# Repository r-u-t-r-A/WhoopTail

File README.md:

# WhoopTail
Battery pigtail pcb with leds

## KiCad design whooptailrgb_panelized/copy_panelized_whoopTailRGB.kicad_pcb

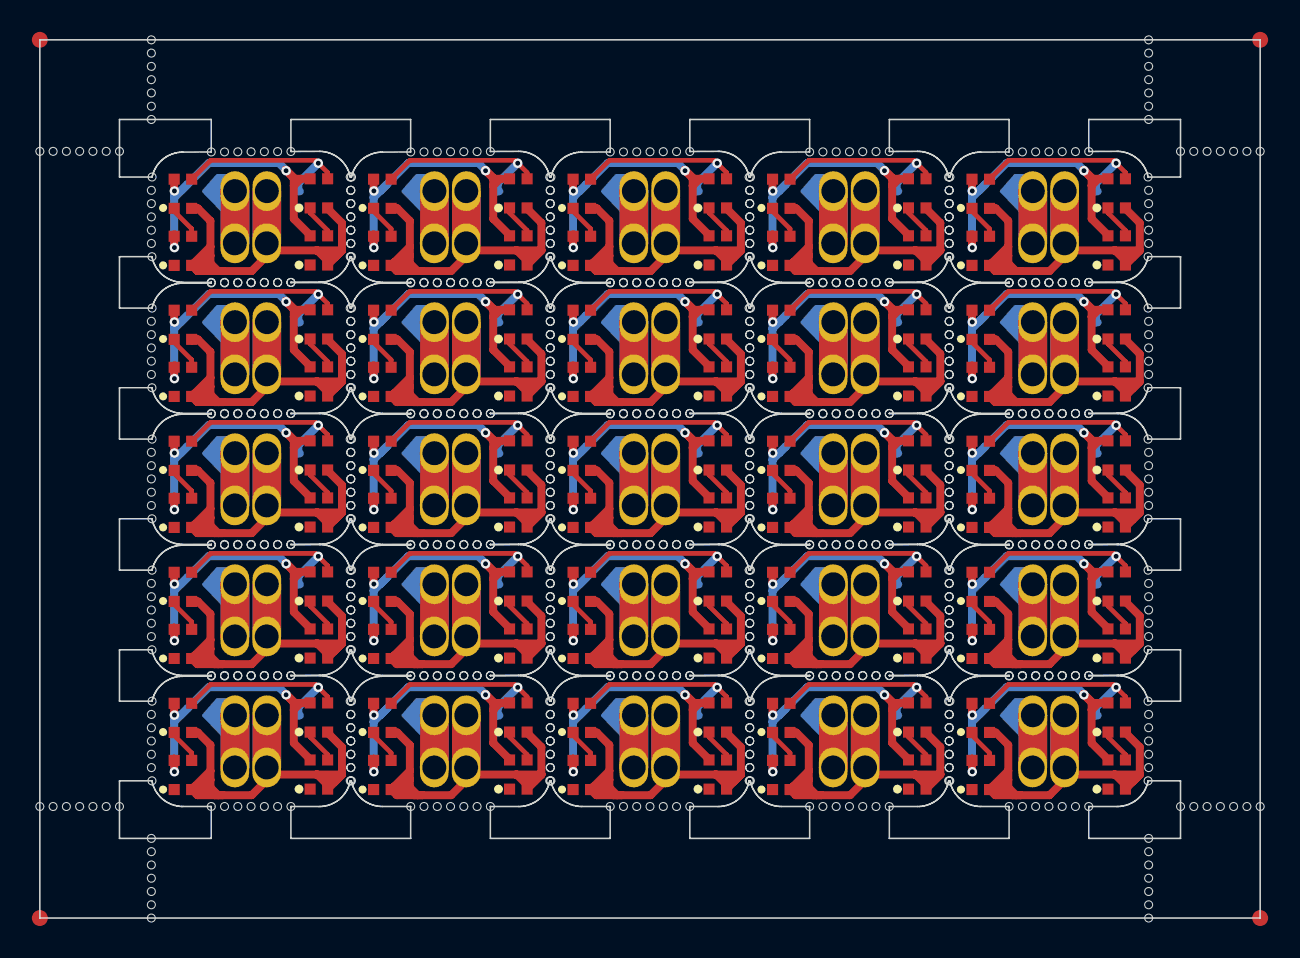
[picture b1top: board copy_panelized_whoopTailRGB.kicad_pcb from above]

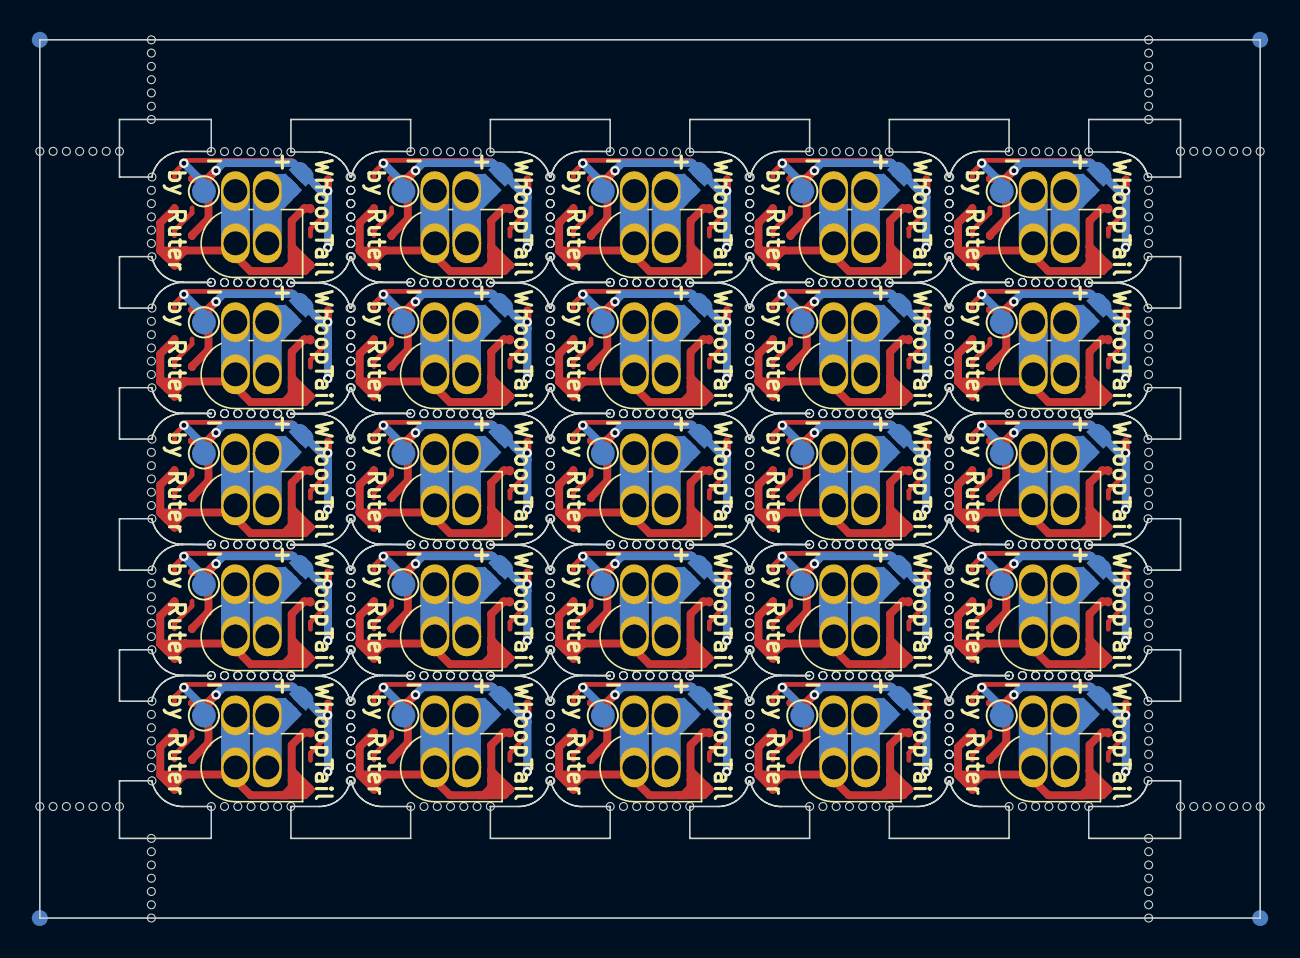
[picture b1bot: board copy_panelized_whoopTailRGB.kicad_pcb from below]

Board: 2 copper layers, 76.6 x 55.1 mm, 964 parts (54 on the bottom side), 150 nets.

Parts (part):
D1, D1#2, D1#3, D1#4, D1#5, D1#6, D1#7, D1#8, D1#9, D1#10, D1#11, D1#12, D1#13, D1#14, D1#15, D1#16, D1#17, D1#18, D1#19, D1#20, D1#21, D1#22, D1#23, D1#24, D1#25, D2, D2#2, D2#3, D2#4, D2#5, D2#6, D2#7, D2#8, D2#9, D2#10, D2#11, D2#12, D2#13, D2#14, D2#15, D2#16, D2#17, D2#18, D2#19, D2#20, D2#21, D2#22, D2#23, D2#24, D2#25, D3, D3#2, D3#3, D3#4, D3#5, D3#6, D3#7, D3#8, D3#9, D3#10, D3#11, D3#12, D3#13, D3#14, D3#15, D3#16, D3#17, D3#18, D3#19, D3#20, D3#21, D3#22, D3#23, D3#24, D3#25, D4, D4#2, D4#3, D4#4, D4#5, D4#6, D4#7, D4#8, D4#9, D4#10, D4#11, D4#12, D4#13, D4#14, D4#15, D4#16, D4#17, D4#18, D4#19, D4#20, D4#21, D4#22, D4#23, D4#24, D4#25: WS2812B-2020; LED_WS2812B-2020_PLCC4_2.0x2.0mm
J1, J1#2, J1#3, J1#4, J1#5, J1#6, J1#7, J1#8, J1#9, J1#10, J1#11, J1#12, J1#13, J1#14, J1#15, J1#16, J1#17, J1#18, J1#19, J1#20, J1#21, J1#22, J1#23, J1#24, J1#25: BT20; PinHeader_1x02_P2.00mm_Vertical
J2, J2#2, J2#3, J2#4, J2#5, J2#6, J2#7, J2#8, J2#9, J2#10, J2#11, J2#12, J2#13, J2#14, J2#15, J2#16, J2#17, J2#18, J2#19, J2#20, J2#21, J2#22, J2#23, J2#24, J2#25: WIRE; PinHeader_1x02_P2.00mm_Vertical
J3, J3#2, J3#3, J3#4, J3#5, J3#6, J3#7, J3#8, J3#9, J3#10, J3#11, J3#12, J3#13, J3#14, J3#15, J3#16, J3#17, J3#18, J3#19, J3#20, J3#21, J3#22, J3#23, J3#24, J3#25: Conn_01x01_Pin; TestPoint_Pad_D1.5mm
J4, J4#2, J4#3, J4#4, J4#5, J4#6, J4#7, J4#8, J4#9, J4#10, J4#11, J4#12, J4#13, J4#14, J4#15, J4#16, J4#17, J4#18, J4#19, J4#20, J4#21, J4#22, J4#23, J4#24, J4#25: Conn_01x02_Pin; SolderJumper-2_P1.3mm_Open_RoundedPad1.0x1.5mm
KiKit_FID_B_1, KiKit_FID_B_2, KiKit_FID_B_3, KiKit_FID_B_4: Fiducial
KiKit_FID_T_1, KiKit_FID_T_2, KiKit_FID_T_3, KiKit_FID_T_4: Fiducial
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
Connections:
Board_0-GND: D1#16.2 (VSS), D2#7.2 (VSS), D3#8.2 (VSS), D4#19.2 (VSS), J1#22.2, J2#14.2
Board_0-Net-(D1-DIN): D1#16.3 (DIN), D3#8.3 (DIN), J3#9.1
Board_0-Net-(D1-DOUT): D1#16.1 (DOUT), D2#7.3 (DIN)
Board_0-Net-(D3-DOUT): D3#8.1 (DOUT), D4#19.3 (DIN)
Board_0-VBAT: J1#22.1, J2#14.1, J4#13.2
Board_0-V_LED: D1#16.4 (VDD), D2#7.4 (VDD), D3#8.4 (VDD), D4#19.4 (VDD), J4#13.1
Board_1-GND: D1#8.2 (VSS), D2#15.2 (VSS), D3#12.2 (VSS), D4#9.2 (VSS), J1#14.2, J2#5.2
Board_1-Net-(D1-DIN): D1#8.3 (DIN), D3#12.3 (DIN), J3#10.1
Board_1-Net-(D1-DOUT): D1#8.1 (DOUT), D2#15.3 (DIN)
Board_1-Net-(D3-DOUT): D3#12.1 (DOUT), D4#9.3 (DIN)
Board_1-VBAT: J1#14.1, J2#5.1, J4#7.2
Board_1-V_LED: D1#8.4 (VDD), D2#15.4 (VDD), D3#12.4 (VDD), D4#9.4 (VDD), J4#7.1
Board_2-GND: D1#11.2 (VSS), D2#18.2 (VSS), D3#11.2 (VSS), D4#14.2 (VSS), J1#17.2, J2#7.2
Board_2-Net-(D1-DIN): D1#11.3 (DIN), D3#11.3 (DIN), J3#16.1
Board_2-Net-(D1-DOUT): D1#11.1 (DOUT), D2#18.3 (DIN)
Board_2-Net-(D3-DOUT): D3#11.1 (DOUT), D4#14.3 (DIN)
Board_2-VBAT: J1#17.1, J2#7.1, J4#8.2
Board_2-V_LED: D1#11.4 (VDD), D2#18.4 (VDD), D3#11.4 (VDD), D4#14.4 (VDD), J4#8.1
Board_3-GND: D1#25.2 (VSS), D2#20.2 (VSS), D3#13.2 (VSS), D4#2.2 (VSS), J1#12.2, J2#23.2
Board_3-Net-(D1-DIN): D1#25.3 (DIN), D3#13.3 (DIN), J3#7.1
Board_3-Net-(D1-DOUT): D1#25.1 (DOUT), D2#20.3 (DIN)
Board_3-Net-(D3-DOUT): D3#13.1 (DOUT), D4#2.3 (DIN)
Board_3-VBAT: J1#12.1, J2#23.1, J4#16.2
Board_3-V_LED: D1#25.4 (VDD), D2#20.4 (VDD), D3#13.4 (VDD), D4#2.4 (VDD), J4#16.1
Board_4-GND: D1#6.2 (VSS), D2#14.2 (VSS), D3#18.2 (VSS), D4#25.2 (VSS), J1#18.2, J2#9.2
Board_4-Net-(D1-DIN): D1#6.3 (DIN), D3#18.3 (DIN), J3#5.1
Board_4-Net-(D1-DOUT): D1#6.1 (DOUT), D2#14.3 (DIN)
Board_4-Net-(D3-DOUT): D3#18.1 (DOUT), D4#25.3 (DIN)
Board_4-VBAT: J1#18.1, J2#9.1, J4#9.2
Board_4-V_LED: D1#6.4 (VDD), D2#14.4 (VDD), D3#18.4 (VDD), D4#25.4 (VDD), J4#9.1
Board_5-GND: D1#5.2 (VSS), D2#5.2 (VSS), D3#9.2 (VSS), D4#20.2 (VSS), J1#16.2, J2#18.2
Board_5-Net-(D1-DIN): D1#5.3 (DIN), D3#9.3 (DIN), J3#19.1
Board_5-Net-(D1-DOUT): D1#5.1 (DOUT), D2#5.3 (DIN)
Board_5-Net-(D3-DOUT): D3#9.1 (DOUT), D4#20.3 (DIN)
Board_5-VBAT: J1#16.1, J2#18.1, J4#5.2
Board_5-V_LED: D1#5.4 (VDD), D2#5.4 (VDD), D3#9.4 (VDD), D4#20.4 (VDD), J4#5.1
Board_6-GND: D1#10.2 (VSS), D2#17.2 (VSS), D3#20.2 (VSS), D4#6.2 (VSS), J1#7.2, J2#4.2
Board_6-Net-(D1-DIN): D1#10.3 (DIN), D3#20.3 (DIN), J3#18.1
Board_6-Net-(D1-DOUT): D1#10.1 (DOUT), D2#17.3 (DIN)
Board_6-Net-(D3-DOUT): D3#20.1 (DOUT), D4#6.3 (DIN)
Board_6-VBAT: J1#7.1, J2#4.1, J4#11.2
Board_6-V_LED: D1#10.4 (VDD), D2#17.4 (VDD), D3#20.4 (VDD), D4#6.4 (VDD), J4#11.1
Board_7-GND: D1#19.2 (VSS), D2#12.2 (VSS), D3#2.2 (VSS), D4#17.2 (VSS), J1#4.2, J2#2.2
Board_7-Net-(D1-DIN): D1#19.3 (DIN), D3#2.3 (DIN), J3#23.1
Board_7-Net-(D1-DOUT): D1#19.1 (DOUT), D2#12.3 (DIN)
Board_7-Net-(D3-DOUT): D3#2.1 (DOUT), D4#17.3 (DIN)
Board_7-VBAT: J1#4.1, J2#2.1, J4#4.2
Board_7-V_LED: D1#19.4 (VDD), D2#12.4 (VDD), D3#2.4 (VDD), D4#17.4 (VDD), J4#4.1
Board_8-GND: D1#2.2 (VSS), D2#8.2 (VSS), D3#25.2 (VSS), D4#24.2 (VSS), J1#15.2, J2#13.2
Board_8-Net-(D1-DIN): D1#2.3 (DIN), D3#25.3 (DIN), J3#8.1
Board_8-Net-(D1-DOUT): D1#2.1 (DOUT), D2#8.3 (DIN)
Board_8-Net-(D3-DOUT): D3#25.1 (DOUT), D4#24.3 (DIN)
Board_8-VBAT: J1#15.1, J2#13.1, J4#20.2
Board_8-V_LED: D1#2.4 (VDD), D2#8.4 (VDD), D3#25.4 (VDD), D4#24.4 (VDD), J4#20.1
Board_9-GND: D1#20.2 (VSS), D2#11.2 (VSS), D3#23.2 (VSS), D4#10.2 (VSS), J1#8.2, J2#22.2
Board_9-Net-(D1-DIN): D1#20.3 (DIN), D3#23.3 (DIN), J3#12.1
Board_9-Net-(D1-DOUT): D1#20.1 (DOUT), D2#11.3 (DIN)
Board_9-Net-(D3-DOUT): D3#23.1 (DOUT), D4#10.3 (DIN)
Board_9-VBAT: J1#8.1, J2#22.1, J4#21.2
Board_9-V_LED: D1#20.4 (VDD), D2#11.4 (VDD), D3#23.4 (VDD), D4#10.4 (VDD), J4#21.1
Board_10-GND: D1#15.2 (VSS), D2#16.2 (VSS), D3#7.2 (VSS), D4#13.2 (VSS), J1#11.2, J2#8.2
Board_10-Net-(D1-DIN): D1#15.3 (DIN), D3#7.3 (DIN), J3#24.1
Board_10-Net-(D1-DOUT): D1#15.1 (DOUT), D2#16.3 (DIN)
Board_10-Net-(D3-DOUT): D3#7.1 (DOUT), D4#13.3 (DIN)
Board_10-VBAT: J1#11.1, J2#8.1, J4#6.2
Board_10-V_LED: D1#15.4 (VDD), D2#16.4 (VDD), D3#7.4 (VDD), D4#13.4 (VDD), J4#6.1
Board_11-GND: D1#14.2 (VSS), D2#19.2 (VSS), D3#19.2 (VSS), D4#16.2 (VSS), J1#3.2, J2#15.2
Board_11-Net-(D1-DIN): D1#14.3 (DIN), D3#19.3 (DIN), J3#3.1
Board_11-Net-(D1-DOUT): D1#14.1 (DOUT), D2#19.3 (DIN)
Board_11-Net-(D3-DOUT): D3#19.1 (DOUT), D4#16.3 (DIN)
Board_11-VBAT: J1#3.1, J2#15.1, J4#3.2
Board_11-V_LED: D1#14.4 (VDD), D2#19.4 (VDD), D3#19.4 (VDD), D4#16.4 (VDD), J4#3.1
Board_12-GND: D1#13.2 (VSS), D2#2.2 (VSS), D3#15.2 (VSS), D4#15.2 (VSS), J1#5.2, J2#21.2
Board_12-Net-(D1-DIN): D1#13.3 (DIN), D3#15.3 (DIN), J3#14.1
Board_12-Net-(D1-DOUT): D1#13.1 (DOUT), D2#2.3 (DIN)
Board_12-Net-(D3-DOUT): D3#15.1 (DOUT), D4#15.3 (DIN)
Board_12-VBAT: J1#5.1, J2#21.1, J4#18.2
Board_12-V_LED: D1#13.4 (VDD), D2#2.4 (VDD), D3#15.4 (VDD), D4#15.4 (VDD), J4#18.1
Board_13-GND: D1#23.2 (VSS), D2#23.2 (VSS), D3#3.2 (VSS), D4#18.2 (VSS), J1#25.2, J2#19.2
Board_13-Net-(D1-DIN): D1#23.3 (DIN), D3#3.3 (DIN), J3#4.1
Board_13-Net-(D1-DOUT): D1#23.1 (DOUT), D2#23.3 (DIN)
Board_13-Net-(D3-DOUT): D3#3.1 (DOUT), D4#18.3 (DIN)
Board_13-VBAT: J1#25.1, J2#19.1, J4#17.2
Board_13-V_LED: D1#23.4 (VDD), D2#23.4 (VDD), D3#3.4 (VDD), D4#18.4 (VDD), J4#17.1
Board_14-GND: D1#17.2 (VSS), D2#4.2 (VSS), D3#4.2 (VSS), D4#11.2 (VSS), J1.2, J2#10.2
Board_14-Net-(D1-DIN): D1#17.3 (DIN), D3#4.3 (DIN), J3#25.1
Board_14-Net-(D1-DOUT): D1#17.1 (DOUT), D2#4.3 (DIN)
Board_14-Net-(D3-DOUT): D3#4.1 (DOUT), D4#11.3 (DIN)
Board_14-VBAT: J1.1, J2#10.1, J4#15.2
Board_14-V_LED: D1#17.4 (VDD), D2#4.4 (VDD), D3#4.4 (VDD), D4#11.4 (VDD), J4#15.1
Board_15-GND: D1#9.2 (VSS), D2#10.2 (VSS), D3#14.2 (VSS), D4#21.2 (VSS), J1#23.2, J2#3.2
Board_15-Net-(D1-DIN): D1#9.3 (DIN), D3#14.3 (DIN), J3#21.1
Board_15-Net-(D1-DOUT): D1#9.1 (DOUT), D2#10.3 (DIN)
Board_15-Net-(D3-DOUT): D3#14.1 (DOUT), D4#21.3 (DIN)
Board_15-VBAT: J1#23.1, J2#3.1, J4#14.2
Board_15-V_LED: D1#9.4 (VDD), D2#10.4 (VDD), D3#14.4 (VDD), D4#21.4 (VDD), J4#14.1
Board_16-GND: D1#4.2 (VSS), D2#22.2 (VSS), D3#17.2 (VSS), D4#12.2 (VSS), J1#6.2, J2#24.2
Board_16-Net-(D1-DIN): D1#4.3 (DIN), D3#17.3 (DIN), J3.1
Board_16-Net-(D1-DOUT): D1#4.1 (DOUT), D2#22.3 (DIN)
Board_16-Net-(D3-DOUT): D3#17.1 (DOUT), D4#12.3 (DIN)
Board_16-VBAT: J1#6.1, J2#24.1, J4#22.2
Board_16-V_LED: D1#4.4 (VDD), D2#22.4 (VDD), D3#17.4 (VDD), D4#12.4 (VDD), J4#22.1
Board_17-GND: D1#22.2 (VSS), D2#25.2 (VSS), D3#10.2 (VSS), D4#3.2 (VSS), J1#10.2, J2.2
Board_17-Net-(D1-DIN): D1#22.3 (DIN), D3#10.3 (DIN), J3#11.1
Board_17-Net-(D1-DOUT): D1#22.1 (DOUT), D2#25.3 (DIN)
Board_17-Net-(D3-DOUT): D3#10.1 (DOUT), D4#3.3 (DIN)
Board_17-VBAT: J1#10.1, J2.1, J4#19.2
Board_17-V_LED: D1#22.4 (VDD), D2#25.4 (VDD), D3#10.4 (VDD), D4#3.4 (VDD), J4#19.1
Board_18-GND: D1.2 (VSS), D2.2 (VSS), D3#16.2 (VSS), D4#4.2 (VSS), J1#19.2, J2#16.2
Board_18-Net-(D1-DIN): D1.3 (DIN), D3#16.3 (DIN), J3#22.1
Board_18-Net-(D1-DOUT): D1.1 (DOUT), D2.3 (DIN)
Board_18-Net-(D3-DOUT): D3#16.1 (DOUT), D4#4.3 (DIN)
Board_18-VBAT: J1#19.1, J2#16.1, J4#12.2
Board_18-V_LED: D1.4 (VDD), D2.4 (VDD), D3#16.4 (VDD), D4#4.4 (VDD), J4#12.1
Board_19-GND: D1#12.2 (VSS), D2#3.2 (VSS), D3#22.2 (VSS), D4#22.2 (VSS), J1#9.2, J2#11.2
Board_19-Net-(D1-DIN): D1#12.3 (DIN), D3#22.3 (DIN), J3#20.1
Board_19-Net-(D1-DOUT): D1#12.1 (DOUT), D2#3.3 (DIN)
Board_19-Net-(D3-DOUT): D3#22.1 (DOUT), D4#22.3 (DIN)
Board_19-VBAT: J1#9.1, J2#11.1, J4#24.2
Board_19-V_LED: D1#12.4 (VDD), D2#3.4 (VDD), D3#22.4 (VDD), D4#22.4 (VDD), J4#24.1
Board_20-GND: D1#24.2 (VSS), D2#21.2 (VSS), D3#5.2 (VSS), D4#5.2 (VSS), J1#20.2, J2#12.2
Board_20-Net-(D1-DIN): D1#24.3 (DIN), D3#5.3 (DIN), J3#13.1
Board_20-Net-(D1-DOUT): D1#24.1 (DOUT), D2#21.3 (DIN)
Board_20-Net-(D3-DOUT): D3#5.1 (DOUT), D4#5.3 (DIN)
Board_20-VBAT: J1#20.1, J2#12.1, J4#2.2
Board_20-V_LED: D1#24.4 (VDD), D2#21.4 (VDD), D3#5.4 (VDD), D4#5.4 (VDD), J4#2.1
Board_21-GND: D1#18.2 (VSS), D2#9.2 (VSS), D3.2 (VSS), D4#7.2 (VSS), J1#21.2, J2#6.2
Board_21-Net-(D1-DIN): D1#18.3 (DIN), D3.3 (DIN), J3#2.1
Board_21-Net-(D1-DOUT): D1#18.1 (DOUT), D2#9.3 (DIN)
Board_21-Net-(D3-DOUT): D3.1 (DOUT), D4#7.3 (DIN)
Board_21-VBAT: J1#21.1, J2#6.1, J4#23.2
Board_21-V_LED: D1#18.4 (VDD), D2#9.4 (VDD), D3.4 (VDD), D4#7.4 (VDD), J4#23.1
Board_22-GND: D1#7.2 (VSS), D2#6.2 (VSS), D3#21.2 (VSS), D4#8.2 (VSS), J1#13.2, J2#17.2
Board_22-Net-(D1-DIN): D1#7.3 (DIN), D3#21.3 (DIN), J3#6.1
Board_22-Net-(D1-DOUT): D1#7.1 (DOUT), D2#6.3 (DIN)
Board_22-Net-(D3-DOUT): D3#21.1 (DOUT), D4#8.3 (DIN)
Board_22-VBAT: J1#13.1, J2#17.1, J4#25.2
Board_22-V_LED: D1#7.4 (VDD), D2#6.4 (VDD), D3#21.4 (VDD), D4#8.4 (VDD), J4#25.1
Board_23-GND: D1#3.2 (VSS), D2#24.2 (VSS), D3#6.2 (VSS), D4.2 (VSS), J1#2.2, J2#20.2
Board_23-Net-(D1-DIN): D1#3.3 (DIN), D3#6.3 (DIN), J3#17.1
Board_23-Net-(D1-DOUT): D1#3.1 (DOUT), D2#24.3 (DIN)
Board_23-Net-(D3-DOUT): D3#6.1 (DOUT), D4.3 (DIN)
Board_23-VBAT: J1#2.1, J2#20.1, J4#10.2
Board_23-V_LED: D1#3.4 (VDD), D2#24.4 (VDD), D3#6.4 (VDD), D4.4 (VDD), J4#10.1
Board_24-GND: D1#21.2 (VSS), D2#13.2 (VSS), D3#24.2 (VSS), D4#23.2 (VSS), J1#24.2, J2#25.2
Board_24-Net-(D1-DIN): D1#21.3 (DIN), D3#24.3 (DIN), J3#15.1
Board_24-Net-(D1-DOUT): D1#21.1 (DOUT), D2#13.3 (DIN)
Board_24-Net-(D3-DOUT): D3#24.1 (DOUT), D4#23.3 (DIN)
Board_24-VBAT: J1#24.1, J2#25.1, J4.2
Board_24-V_LED: D1#21.4 (VDD), D2#13.4 (VDD), D3#24.4 (VDD), D4#23.4 (VDD), J4.1

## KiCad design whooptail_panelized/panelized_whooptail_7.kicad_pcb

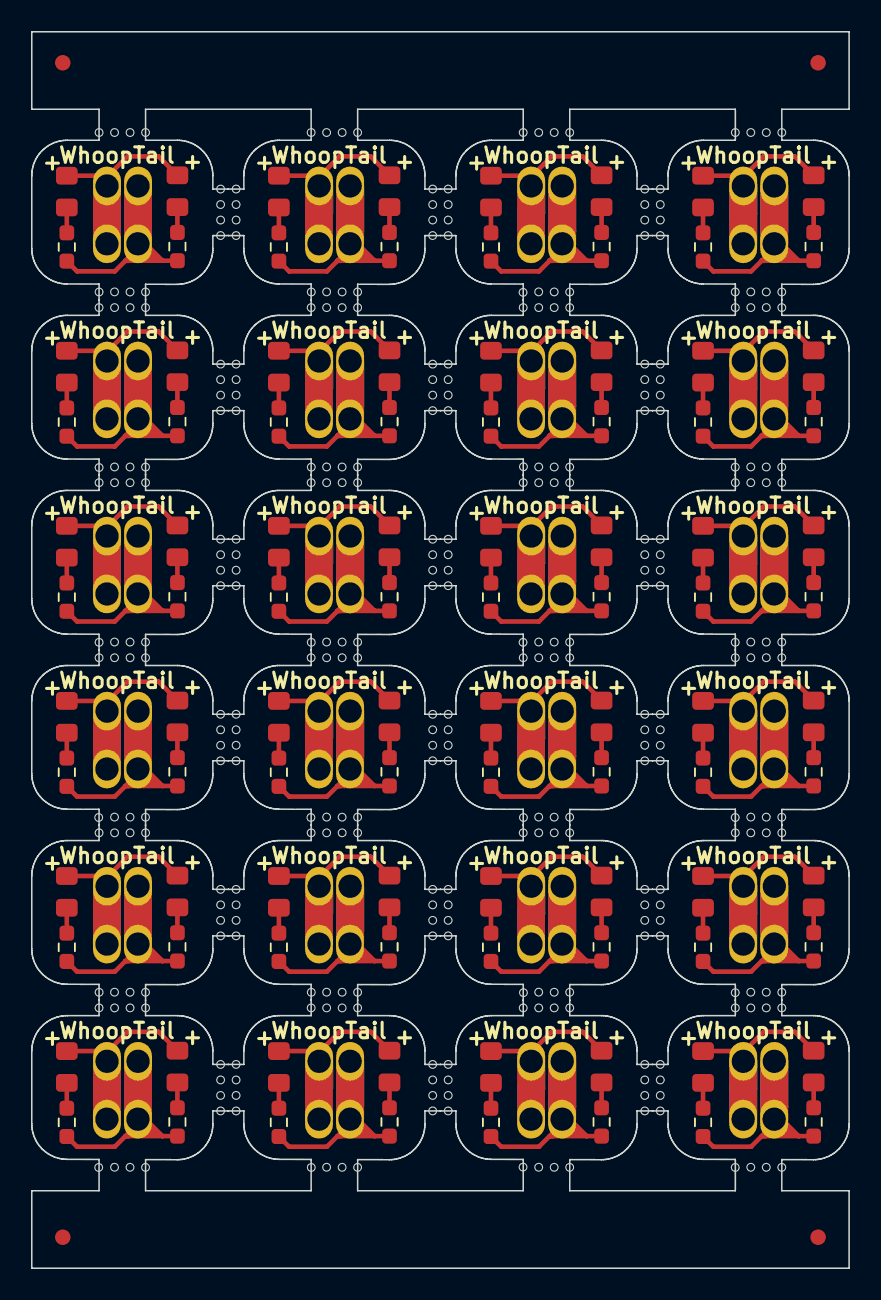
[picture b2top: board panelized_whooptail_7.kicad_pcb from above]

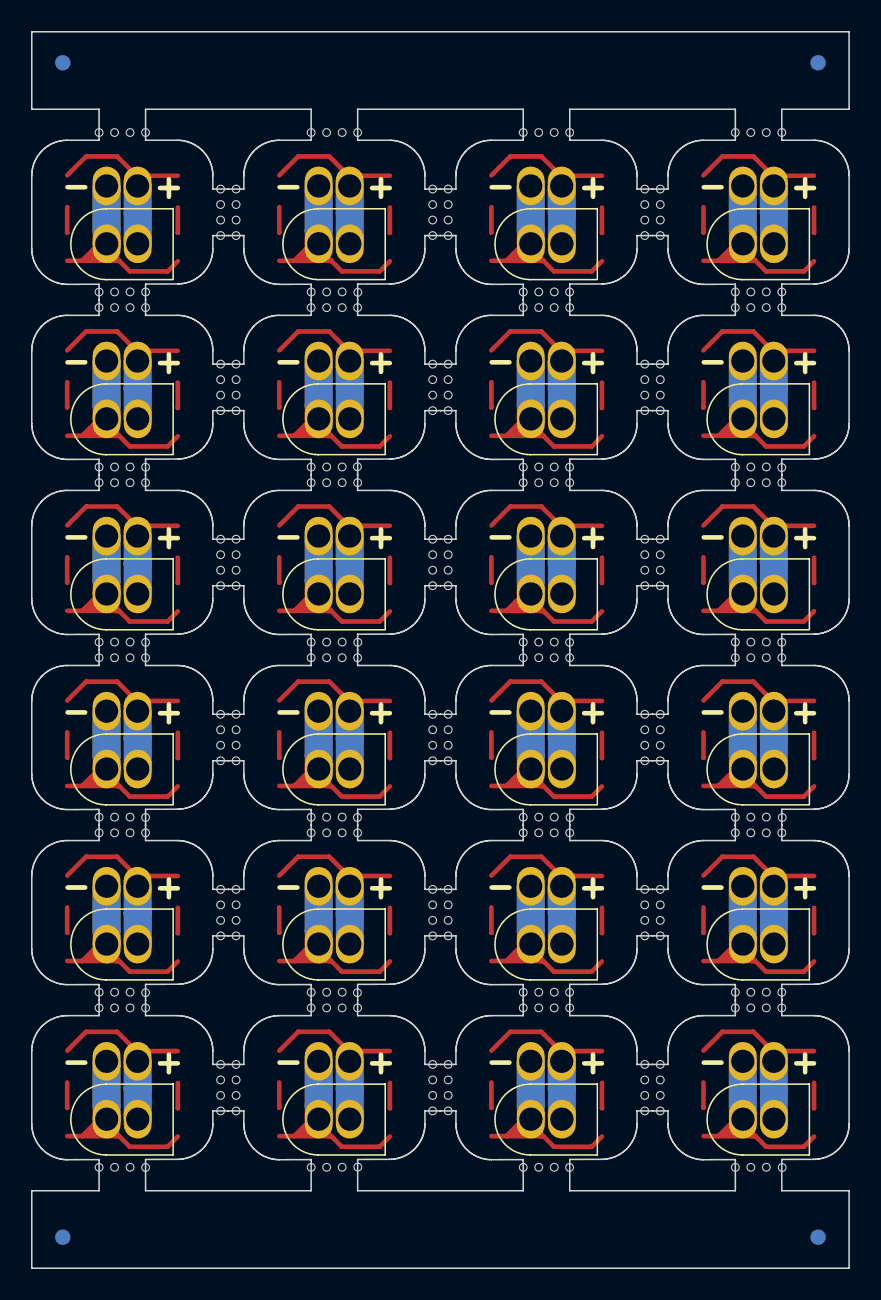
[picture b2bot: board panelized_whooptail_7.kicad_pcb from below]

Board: 2 copper layers, 52.7 x 79.8 mm, 488 parts (28 on the bottom side), 96 nets.

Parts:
D1, D1_2, D1_3, D1_4, D1_5, D1_6, D1_7, D1_8, D1_9, D1_10, D1_11, D1_12, D1_13, D1_14, D1_15, D1_16, D1_17, D1_18, D1_19, D1_20, D1_21, D1_22, D1_23, D1_24, D2, D2_2, D2_3, D2_4, D2_5, D2_6, D2_7, D2_8, D2_9, D2_10, D2_11, D2_12, D2_13, D2_14, D2_15, D2_16, D2_17, D2_18, D2_19, D2_20, D2_21, D2_22, D2_23, D2_24: LED; LED_0805_2012Metric_Pad1.15x1.40mm_HandSolder
J1, J1#2, J1#3, J1#4, J1#5, J1#6, J1#7, J1#8, J1#9, J1#10, J1#11, J1#12, J1#13, J1#14, J1#15, J1#16, J1#17, J1#18, J1#19, J1#20, J1#21, J1#22, J1#23, J1#24: BT20; PinHeader_1x02_P2.00mm_Vertical
J2, J2#2, J2#3, J2#4, J2#5, J2#6, J2#7, J2#8, J2#9, J2#10, J2#11, J2#12, J2#13, J2#14, J2#15, J2#16, J2#17, J2#18, J2#19, J2#20, J2#21, J2#22, J2#23, J2#24: WIRES; PinHeader_1x02_P2.00mm_Vertical
KiKit_FID_B_1, KiKit_FID_B_2, KiKit_FID_B_3, KiKit_FID_B_4: Fiducial
KiKit_FID_T_1, KiKit_FID_T_2, KiKit_FID_T_3, KiKit_FID_T_4: Fiducial
KiKit_MB_1_1, KiKit_MB_1_2, KiKit_MB_1_3, KiKit_MB_1_4, KiKit_MB_2_1, KiKit_MB_2_2, KiKit_MB_2_3, KiKit_MB_2_4, KiKit_MB_3_1, KiKit_MB_3_2, KiKit_MB_3_3, KiKit_MB_4_1, KiKit_MB_4_2, KiKit_MB_4_3, KiKit_MB_4_4, KiKit_MB_5_1, KiKit_MB_5_2, KiKit_MB_5_3, KiKit_MB_5_4, KiKit_MB_6_1, KiKit_MB_6_2, KiKit_MB_6_3, KiKit_MB_6_4, KiKit_MB_7_1, KiKit_MB_7_2, KiKit_MB_7_3, KiKit_MB_8_1, KiKit_MB_8_2, KiKit_MB_8_3, KiKit_MB_8_4, KiKit_MB_9_1, KiKit_MB_9_2, KiKit_MB_9_3, KiKit_MB_9_4, KiKit_MB_10_1, KiKit_MB_10_2, KiKit_MB_10_3, KiKit_MB_10_4, KiKit_MB_11_1, KiKit_MB_11_2, KiKit_MB_11_3, KiKit_MB_12_1, KiKit_MB_12_2, KiKit_MB_12_3, KiKit_MB_12_4, KiKit_MB_13_1, KiKit_MB_13_2, KiKit_MB_13_3, KiKit_MB_13_4, KiKit_MB_14_1, KiKit_MB_14_2, KiKit_MB_14_3, KiKit_MB_15_1, KiKit_MB_15_2, KiKit_MB_15_3, KiKit_MB_15_4, KiKit_MB_16_1, KiKit_MB_16_2, KiKit_MB_16_3, KiKit_MB_16_4, KiKit_MB_17_1, KiKit_MB_17_2, KiKit_MB_17_3, KiKit_MB_18_1, KiKit_MB_18_2, KiKit_MB_18_3, KiKit_MB_18_4, KiKit_MB_19_1, KiKit_MB_19_2, KiKit_MB_19_3, KiKit_MB_19_4, KiKit_MB_20_1, KiKit_MB_20_2, KiKit_MB_20_3, KiKit_MB_20_4, KiKit_MB_21_1, KiKit_MB_21_2, KiKit_MB_21_3, KiKit_MB_22_1, KiKit_MB_22_2, KiKit_MB_22_3, KiKit_MB_22_4, KiKit_MB_23_1, KiKit_MB_23_2, KiKit_MB_23_3, KiKit_MB_23_4, KiKit_MB_24_1, KiKit_MB_24_2, KiKit_MB_24_3, KiKit_MB_24_4, KiKit_MB_25_1, KiKit_MB_25_2, KiKit_MB_25_3, KiKit_MB_26_1, KiKit_MB_26_2, KiKit_MB_26_3, KiKit_MB_26_4, KiKit_MB_27_1, KiKit_MB_27_2, KiKit_MB_27_3, KiKit_MB_27_4, KiKit_MB_28_1, KiKit_MB_28_2, KiKit_MB_28_3, KiKit_MB_29_1, KiKit_MB_29_2, KiKit_MB_29_3, KiKit_MB_29_4, KiKit_MB_30_1, KiKit_MB_30_2, KiKit_MB_30_3, KiKit_MB_30_4, KiKit_MB_31_1, KiKit_MB_31_2, KiKit_MB_31_3, KiKit_MB_32_1, KiKit_MB_32_2, KiKit_MB_32_3, KiKit_MB_32_4, KiKit_MB_33_1, KiKit_MB_33_2, KiKit_MB_33_3, KiKit_MB_33_4, KiKit_MB_34_1, KiKit_MB_34_2, KiKit_MB_34_3, KiKit_MB_34_4, KiKit_MB_35_1, KiKit_MB_35_2, KiKit_MB_35_3, KiKit_MB_36_1, KiKit_MB_36_2, KiKit_MB_36_3, KiKit_MB_36_4, KiKit_MB_37_1, KiKit_MB_37_2, KiKit_MB_37_3, KiKit_MB_37_4, KiKit_MB_38_1, KiKit_MB_38_2, KiKit_MB_38_3, KiKit_MB_38_4, KiKit_MB_39_1, KiKit_MB_39_2, KiKit_MB_39_3, KiKit_MB_40_1, KiKit_MB_40_2, KiKit_MB_40_3, KiKit_MB_40_4, KiKit_MB_41_1, KiKit_MB_41_2, KiKit_MB_41_3, KiKit_MB_41_4, KiKit_MB_42_1, KiKit_MB_42_2, KiKit_MB_42_3, KiKit_MB_43_1, KiKit_MB_43_2, KiKit_MB_43_3, KiKit_MB_43_4, KiKit_MB_44_1, KiKit_MB_44_2, KiKit_MB_44_3, KiKit_MB_44_4, KiKit_MB_45_1, KiKit_MB_45_2, KiKit_MB_45_3, KiKit_MB_46_1, KiKit_MB_46_2, KiKit_MB_46_3, KiKit_MB_46_4, KiKit_MB_47_1, KiKit_MB_47_2, KiKit_MB_47_3, KiKit_MB_47_4, KiKit_MB_48_1, KiKit_MB_48_2, KiKit_MB_48_3, KiKit_MB_48_4, KiKit_MB_49_1, KiKit_MB_49_2, KiKit_MB_49_3, KiKit_MB_50_1, KiKit_MB_50_2, KiKit_MB_50_3, KiKit_MB_50_4, KiKit_MB_51_1, KiKit_MB_51_2, KiKit_MB_51_3, KiKit_MB_51_4, KiKit_MB_52_1, KiKit_MB_52_2, KiKit_MB_52_3, KiKit_MB_52_4, KiKit_MB_53_1, KiKit_MB_53_2, KiKit_MB_53_3, KiKit_MB_54_1, KiKit_MB_54_2, KiKit_MB_54_3, KiKit_MB_54_4, KiKit_MB_55_1, KiKit_MB_55_2, KiKit_MB_55_3, KiKit_MB_55_4, KiKit_MB_56_1, KiKit_MB_56_2, KiKit_MB_56_3, KiKit_MB_57_1, KiKit_MB_57_2, KiKit_MB_57_3, KiKit_MB_57_4, KiKit_MB_58_1, KiKit_MB_58_2, KiKit_MB_58_3, KiKit_MB_58_4, KiKit_MB_59_1, KiKit_MB_59_2, KiKit_MB_59_3, KiKit_MB_60_1, KiKit_MB_60_2, KiKit_MB_60_3, KiKit_MB_60_4, KiKit_MB_61_1, KiKit_MB_61_2, KiKit_MB_61_3, KiKit_MB_61_4, KiKit_MB_62_1, KiKit_MB_62_2, KiKit_MB_62_3, KiKit_MB_62_4, KiKit_MB_63_1, KiKit_MB_63_2, KiKit_MB_63_3, KiKit_MB_64_1, KiKit_MB_64_2, KiKit_MB_64_3, KiKit_MB_64_4, KiKit_MB_65_1, KiKit_MB_65_2, KiKit_MB_65_3, KiKit_MB_65_4, KiKit_MB_66_1, KiKit_MB_66_2, KiKit_MB_66_3, KiKit_MB_66_4, KiKit_MB_67_1, KiKit_MB_67_2, KiKit_MB_67_3, KiKit_MB_68_1, KiKit_MB_68_2, KiKit_MB_68_3, KiKit_MB_68_4, KiKit_MB_69_1, KiKit_MB_69_2, KiKit_MB_69_3, KiKit_MB_69_4, KiKit_MB_70_1, KiKit_MB_70_2, KiKit_MB_70_3, KiKit_MB_71_1, KiKit_MB_71_2, KiKit_MB_71_3, KiKit_MB_71_4, KiKit_MB_72_1, KiKit_MB_72_2, KiKit_MB_72_3, KiKit_MB_72_4, KiKit_MB_73_1, KiKit_MB_73_2, KiKit_MB_73_3, KiKit_MB_73_3#2, KiKit_MB_73_3#3, KiKit_MB_73_3#4, KiKit_MB_73_3#5, KiKit_MB_73_3#6, KiKit_MB_73_3#7, KiKit_MB_73_3#8, KiKit_MB_73_3#9, KiKit_MB_73_3#10, KiKit_MB_73_3#11, KiKit_MB_73_3#12, KiKit_MB_73_3#13, KiKit_MB_73_3#14, KiKit_MB_73_3#15, KiKit_MB_73_3#16, KiKit_MB_73_3#17, KiKit_MB_73_3#18, KiKit_MB_73_3#19, KiKit_MB_73_3#20, KiKit_MB_73_3#21, KiKit_MB_73_3#22, KiKit_MB_73_3#23, KiKit_MB_73_3#24, KiKit_MB_73_3#25, KiKit_MB_74_1, KiKit_MB_74_2, KiKit_MB_74_3, KiKit_MB_74_4, KiKit_MB_75_1, KiKit_MB_75_2, KiKit_MB_75_3, KiKit_MB_75_4, KiKit_MB_76_1, KiKit_MB_76_2, KiKit_MB_76_3, KiKit_MB_76_4, KiKit_MB_77_1, KiKit_MB_77_2, KiKit_MB_77_3, KiKit_MB_78_1, KiKit_MB_78_2, KiKit_MB_78_3, KiKit_MB_78_4, KiKit_MB_79_1, KiKit_MB_79_2, KiKit_MB_79_3, KiKit_MB_79_4, KiKit_MB_80_1, KiKit_MB_80_2, KiKit_MB_80_3, KiKit_MB_80_4, KiKit_MB_81_1, KiKit_MB_81_2, KiKit_MB_81_3, KiKit_MB_82_1, KiKit_MB_82_2, KiKit_MB_82_3, KiKit_MB_82_4, KiKit_MB_83_1, KiKit_MB_83_2, KiKit_MB_83_3, KiKit_MB_83_4, KiKit_MB_84_1, KiKit_MB_84_2, KiKit_MB_84_3: NPTH
R1, R1_2, R1_3, R1_4, R1_5, R1_6, R1_7, R1_8, R1_9, R1_10, R1_11, R1_12, R1_13, R1_14, R1_15, R1_16, R1_17, R1_18, R1_19, R1_20, R1_21, R1_22, R1_23, R1_24, R2, R2_2, R2_3, R2_4, R2_5, R2_6, R2_7, R2_8, R2_9, R2_10, R2_11, R2_12, R2_13, R2_14, R2_15, R2_16, R2_17, R2_18, R2_19, R2_20, R2_21, R2_22, R2_23, R2_24: R; R_0603_1608Metric_Pad0.98x0.95mm_HandSolder

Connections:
Board_0-GND: J1#23.2, J2#17.2, R1.2, R2.2
Board_0-Net-(D1-K): D1.1 (K), R1.1
Board_0-Net-(D2-K): D2.1 (K), R2.1
Board_0-VBAT: D1.2 (A), D2.2 (A), J1#23.1, J2#17.1
Board_1-GND: J1#22.2, J2#24.2, R1_7.2, R2_7.2
Board_1-Net-(D1-K): D1_7.1 (K), R1_7.1
Board_1-Net-(D2-K): D2_7.1 (K), R2_7.1
Board_1-VBAT: D1_7.2 (A), D2_7.2 (A), J1#22.1, J2#24.1
Board_2-GND: J1.2, J2#20.2, R1_13.2, R2_13.2
Board_2-Net-(D1-K): D1_13.1 (K), R1_13.1
Board_2-Net-(D2-K): D2_13.1 (K), R2_13.1
Board_2-VBAT: D1_13.2 (A), D2_13.2 (A), J1.1, J2#20.1
Board_3-GND: J1#10.2, J2#11.2, R1_19.2, R2_19.2
Board_3-Net-(D1-K): D1_19.1 (K), R1_19.1
Board_3-Net-(D2-K): D2_19.1 (K), R2_19.1
Board_3-VBAT: D1_19.2 (A), D2_19.2 (A), J1#10.1, J2#11.1
Board_4-GND: J1#16.2, J2#4.2, R1_2.2, R2_2.2
Board_4-Net-(D1-K): D1_2.1 (K), R1_2.1
Board_4-Net-(D2-K): D2_2.1 (K), R2_2.1
Board_4-VBAT: D1_2.2 (A), D2_2.2 (A), J1#16.1, J2#4.1
Board_5-GND: J1#17.2, J2#6.2, R1_8.2, R2_8.2
Board_5-Net-(D1-K): D1_8.1 (K), R1_8.1
Board_5-Net-(D2-K): D2_8.1 (K), R2_8.1
Board_5-VBAT: D1_8.2 (A), D2_8.2 (A), J1#17.1, J2#6.1
Board_6-GND: J1#21.2, J2#23.2, R1_14.2, R2_14.2
Board_6-Net-(D1-K): D1_14.1 (K), R1_14.1
Board_6-Net-(D2-K): D2_14.1 (K), R2_14.1
Board_6-VBAT: D1_14.2 (A), D2_14.2 (A), J1#21.1, J2#23.1
Board_7-GND: J1#7.2, J2#3.2, R1_20.2, R2_20.2
Board_7-Net-(D1-K): D1_20.1 (K), R1_20.1
Board_7-Net-(D2-K): D2_20.1 (K), R2_20.1
Board_7-VBAT: D1_20.2 (A), D2_20.2 (A), J1#7.1, J2#3.1
Board_8-GND: J1#19.2, J2#18.2, R1_3.2, R2_3.2
Board_8-Net-(D1-K): D1_3.1 (K), R1_3.1
Board_8-Net-(D2-K): D2_3.1 (K), R2_3.1
Board_8-VBAT: D1_3.2 (A), D2_3.2 (A), J1#19.1, J2#18.1
Board_9-GND: J1#2.2, J2#15.2, R1_9.2, R2_9.2
Board_9-Net-(D1-K): D1_9.1 (K), R1_9.1
Board_9-Net-(D2-K): D2_9.1 (K), R2_9.1
Board_9-VBAT: D1_9.2 (A), D2_9.2 (A), J1#2.1, J2#15.1
Board_10-GND: J1#3.2, J2#14.2, R1_15.2, R2_15.2
Board_10-Net-(D1-K): D1_15.1 (K), R1_15.1
Board_10-Net-(D2-K): D2_15.1 (K), R2_15.1
Board_10-VBAT: D1_15.2 (A), D2_15.2 (A), J1#3.1, J2#14.1
Board_11-GND: J1#5.2, J2#10.2, R1_21.2, R2_21.2
Board_11-Net-(D1-K): D1_21.1 (K), R1_21.1
Board_11-Net-(D2-K): D2_21.1 (K), R2_21.1
Board_11-VBAT: D1_21.2 (A), D2_21.2 (A), J1#5.1, J2#10.1
Board_12-GND: J1#20.2, J2.2, R1_4.2, R2_4.2
Board_12-Net-(D1-K): D1_4.1 (K), R1_4.1
Board_12-Net-(D2-K): D2_4.1 (K), R2_4.1
Board_12-VBAT: D1_4.2 (A), D2_4.2 (A), J1#20.1, J2.1
Board_13-GND: J1#4.2, J2#22.2, R1_10.2, R2_10.2
Board_13-Net-(D1-K): D1_10.1 (K), R1_10.1
Board_13-Net-(D2-K): D2_10.1 (K), R2_10.1
Board_13-VBAT: D1_10.2 (A), D2_10.2 (A), J1#4.1, J2#22.1
Board_14-GND: J1#24.2, J2#16.2, R1_16.2, R2_16.2
Board_14-Net-(D1-K): D1_16.1 (K), R1_16.1
Board_14-Net-(D2-K): D2_16.1 (K), R2_16.1
Board_14-VBAT: D1_16.2 (A), D2_16.2 (A), J1#24.1, J2#16.1
Board_15-GND: J1#13.2, J2#2.2, R1_22.2, R2_22.2
Board_15-Net-(D1-K): D1_22.1 (K), R1_22.1
Board_15-Net-(D2-K): D2_22.1 (K), R2_22.1
Board_15-VBAT: D1_22.2 (A), D2_22.2 (A), J1#13.1, J2#2.1
Board_16-GND: J1#11.2, J2#7.2, R1_5.2, R2_5.2
Board_16-Net-(D1-K): D1_5.1 (K), R1_5.1
Board_16-Net-(D2-K): D2_5.1 (K), R2_5.1
Board_16-VBAT: D1_5.2 (A), D2_5.2 (A), J1#11.1, J2#7.1
Board_17-GND: J1#18.2, J2#21.2, R1_11.2, R2_11.2
Board_17-Net-(D1-K): D1_11.1 (K), R1_11.1
Board_17-Net-(D2-K): D2_11.1 (K), R2_11.1
Board_17-VBAT: D1_11.2 (A), D2_11.2 (A), J1#18.1, J2#21.1
Board_18-GND: J1#9.2, J2#5.2, R1_17.2, R2_17.2
Board_18-Net-(D1-K): D1_17.1 (K), R1_17.1
Board_18-Net-(D2-K): D2_17.1 (K), R2_17.1
Board_18-VBAT: D1_17.2 (A), D2_17.2 (A), J1#9.1, J2#5.1
Board_19-GND: J1#14.2, J2#12.2, R1_23.2, R2_23.2
Board_19-Net-(D1-K): D1_23.1 (K), R1_23.1
Board_19-Net-(D2-K): D2_23.1 (K), R2_23.1
Board_19-VBAT: D1_23.2 (A), D2_23.2 (A), J1#14.1, J2#12.1
Board_20-GND: J1#6.2, J2#9.2, R1_6.2, R2_6.2
Board_20-Net-(D1-K): D1_6.1 (K), R1_6.1
Board_20-Net-(D2-K): D2_6.1 (K), R2_6.1
Board_20-VBAT: D1_6.2 (A), D2_6.2 (A), J1#6.1, J2#9.1
Board_21-GND: J1#12.2, J2#13.2, R1_12.2, R2_12.2
Board_21-Net-(D1-K): D1_12.1 (K), R1_12.1
Board_21-Net-(D2-K): D2_12.1 (K), R2_12.1
Board_21-VBAT: D1_12.2 (A), D2_12.2 (A), J1#12.1, J2#13.1
Board_22-GND: J1#8.2, J2#19.2, R1_18.2, R2_18.2
Board_22-Net-(D1-K): D1_18.1 (K), R1_18.1
Board_22-Net-(D2-K): D2_18.1 (K), R2_18.1
Board_22-VBAT: D1_18.2 (A), D2_18.2 (A), J1#8.1, J2#19.1
Board_23-GND: J1#15.2, J2#8.2, R1_24.2, R2_24.2
Board_23-Net-(D1-K): D1_24.1 (K), R1_24.1
Board_23-Net-(D2-K): D2_24.1 (K), R2_24.1
Board_23-VBAT: D1_24.2 (A), D2_24.2 (A), J1#15.1, J2#8.1

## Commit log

2025-11-23 Add image to README for PCB visual reference
    Added image to README for visual reference.
2025-12-10 Add BOM with components and resistor calculations
    Added a Bill of Materials (BOM) with components and resistor calculations for different LED colors.
2026-03-28 dodane spanelizowane pcb
